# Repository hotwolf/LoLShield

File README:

This is the website of the LoLSnakes project.

...see https://hotwolf.github.io/LoLSnakes/

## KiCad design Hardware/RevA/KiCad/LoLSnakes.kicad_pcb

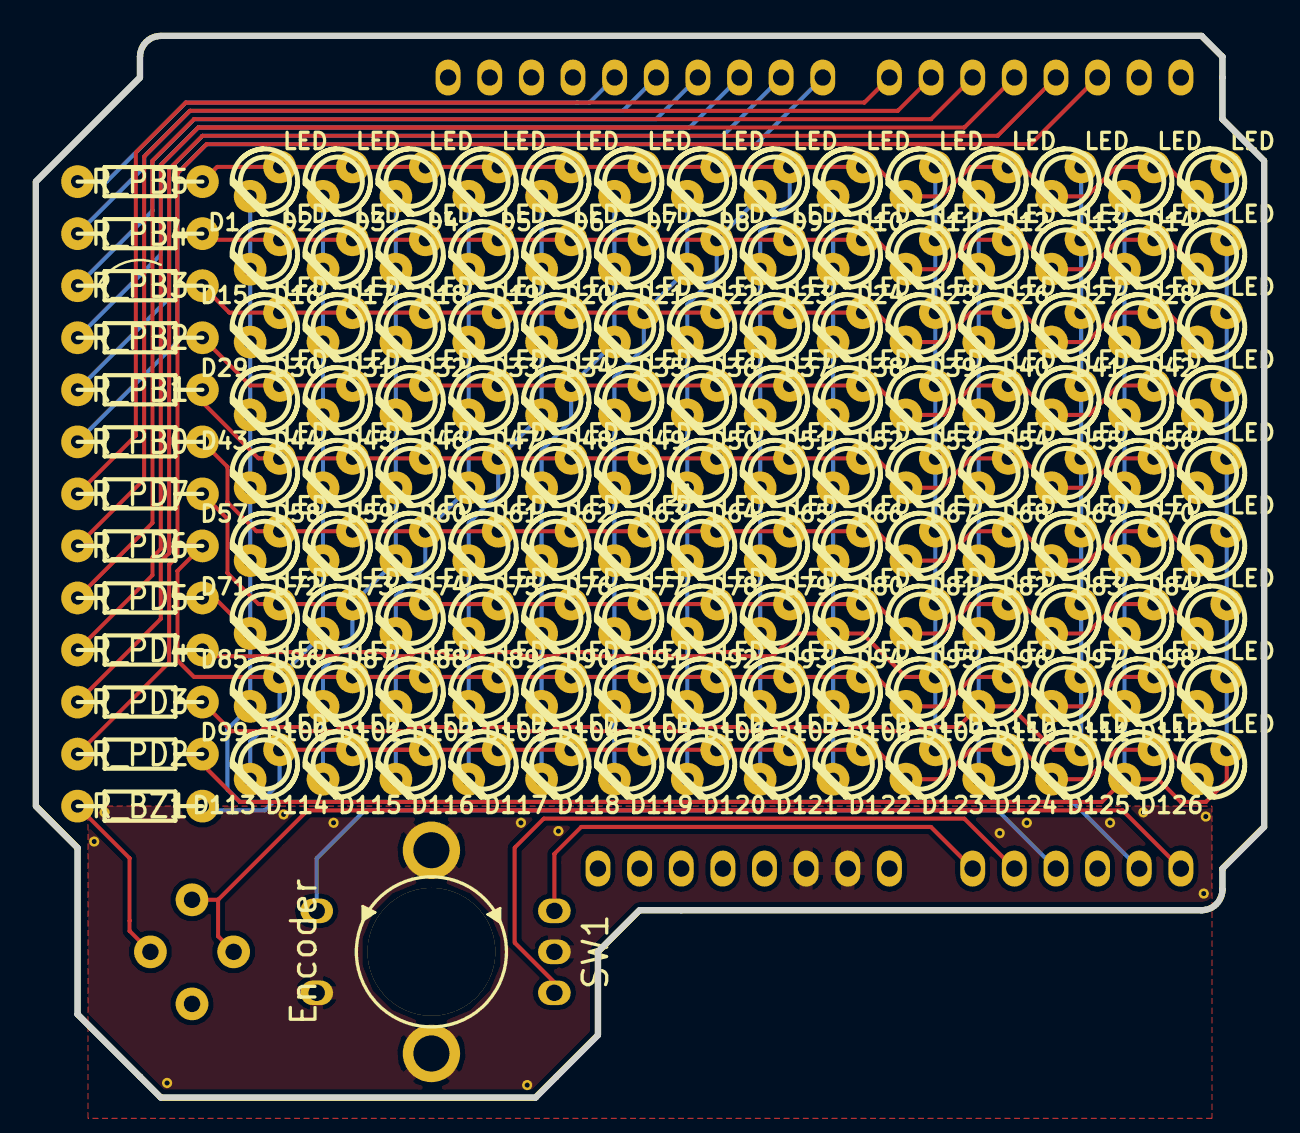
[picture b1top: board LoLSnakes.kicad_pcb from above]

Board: 2 copper layers, 74.9 x 64.8 mm, 156 parts (1 on the bottom side), 31 nets.

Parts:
BZ1: BUZZER; buzzer
D1, D2, D3, D4, D5, D6, D7, D8, D9, D10, D11, D12, D13, D14, D15, D16, D17, D18, D19, D20, D21, D22, D23, D24, D25, D26, D27, D28, D29, D30, D31, D32, D33, D34, D35, D36, D37, D38, D39, D40, D41, D42, D43, D44, D45, D46, D47, D48, D49, D50, D51, D52, D53, D54, D55, D56, D57, D58, D59, D60, D61, D62, D63, D64, D65, D66, D67, D68, D69, D70, D71, D72, D73, D74, D75, D76, D77, D78, D79, D80, D81, D82, D83, D84, D85, D86, D87, D88, D89, D90, D91, D92, D93, D94, D95, D96, D97, D98, D99, D100, D101, D102, D103, D104, D105, D106, D107, D108, D109, D110, D111, D112, D113, D114, D115, D116, D117, D118, D119, D120, D121, D122, D123, D124, D125, D126: LED; led_3mm_clear
J1: ARDUINO; arduino_header_extended
R_BZ1: R; rc03
R_PB0, R_PB1, R_PB2, R_PB3, R_PB4, R_PB5: R; rc03
R_PD2, R_PD3, R_PD4, R_PD5, R_PD6, R_PD7: R; rc03
SW1: Encoder; encoder_lowered
VIA: GND; via
VIA#2, VIA#3, VIA#4, VIA#5, VIA#6, VIA#7, VIA#8, VIA#9, VIA#10, VIA#11, VIA#12, VIA#13, VIA#14: GND; via

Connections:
/PB0: J1.23, R_PB0.1
/PB0_R: D4.1, D18.1, D32.1, D46.1, D60.1, D71.2, D72.2, D73.2, D74.2, D75.2, D76.2, D77.2, D78.2, D79.2, D80.1, D81.2, D82.1, D83.2, D84.1, D87.1, D101.1, D115.1, R_PB0.2
/PB1: J1.24, R_PB1.1
/PB1_R: D5.1, D19.1, D33.1, D47.1, D57.2, D58.2, D59.2, D60.2, D61.2, D62.2, D63.2, D64.2, D65.2, D66.1, D67.2, D68.1, D69.2, D70.1, D74.1, D88.1, D102.1, D116.1, R_PB1.2
/PB2: J1.25, R_PB2.1
/PB2_R: D6.1, D20.1, D34.1, D43.2, D44.2, D45.2, D46.2, D47.2, D48.2, D49.2, D50.2, D51.2, D52.1, D53.2, D54.1, D55.2, D56.1, D61.1, D75.1, D89.1, D103.1, D117.1, R_PB2.2
/PB3: J1.26, R_PB3.1
/PB3_R: D7.1, D21.1, D29.2, D30.2, D31.2, D32.2, D33.2, D34.2, D35.2, D36.2, D37.2, D38.1, D39.2, D40.1, D41.2, D42.1, D48.1, D62.1, D76.1, D90.1, D104.1, D118.1, R_PB3.2
/PB4: J1.27, R_PB4.1
/PB4_R: D8.1, D15.2, D16.2, D17.2, D18.2, D19.2, D20.2, D21.2, D22.2, D23.2, D24.1, D25.2, D26.1, D27.2, D28.1, D35.1, D49.1, D63.1, D77.1, D91.1, D105.1, D119.1, R_PB4.2
/PB5: J1.28, R_PB5.1
/PB5_R: D1.2, D2.2, D3.2, D4.2, D5.2, D6.2, D7.2, D8.2, D9.2, D10.1, D11.2, D12.1, D13.2, D14.1, D22.1, D36.1, D50.1, D64.1, D78.1, D92.1, D106.1, D120.1, R_PB5.2
/PD2: J1.17, R_PD2.1
/PD2_R: D13.1, D14.2, D27.1, D28.2, D41.1, D42.2, D55.1, D56.2, D69.1, D70.2, D83.1, D84.2, D97.1, D98.2, D111.1, D112.2, D125.1, D126.2, R_PD2.2
/PD3: J1.18, R_PD3.1
/PD3_R: D11.1, D12.2, D25.1, D26.2, D39.1, D40.2, D53.1, D54.2, D67.1, D68.2, D81.1, D82.2, D95.1, D96.2, D109.1, D110.2, D123.1, D124.2, R_PD3.2
/PD4: J1.19, R_PD4.1
/PD4_R: D9.1, D10.2, D23.1, D24.2, D37.1, D38.2, D51.1, D52.2, D65.1, D66.2, D79.1, D80.2, D93.1, D94.2, D107.1, D108.2, D121.1, D122.2, R_PD4.2
/PD5: J1.20, R_PD5.1
/PD5_R: D1.1, D15.1, D29.1, D43.1, D57.1, D71.1, D85.1, D99.1, D113.2, D114.2, D115.2, D116.2, D117.2, D118.2, D119.2, D120.2, D121.2, D122.1, D123.2, D124.1, D125.2, D126.1, R_PD5.2
/PD6: J1.21, R_PD6.1
/PD6_R: D2.1, D16.1, D30.1, D44.1, D58.1, D72.1, D86.1, D99.2, D100.2, D101.2, D102.2, D103.2, D104.2, D105.2, D106.2, D107.2, D108.1, D109.2, D110.1, D111.2, D112.1, D113.1, R_PD6.2
/PD7: J1.22, R_PD7.1
/PD7_R: D3.1, D17.1, D31.1, D45.1, D59.1, D73.1, D85.2, D86.2, D87.2, D88.2, D89.2, D90.2, D91.2, D92.2, D93.2, D94.1, D95.2, D96.1, D97.2, D98.1, D100.1, D114.1, R_PD7.2
GND: J1.6, J1.7, SW1.2, SW1.5, SW1.6, VIA.1, VIA#2.1, VIA#3.1, VIA#4.1, VIA#5.1, VIA#6.1, VIA#7.1, VIA#8.1, VIA#9.1, VIA#10.1, VIA#11.1, VIA#12.1, VIA#13.1, VIA#14.1
unnamed: BZ1.1, J1.14
unnamed: BZ1.2, R_BZ1.2
unnamed: J1.9, SW1.3
unnamed: J1.10, SW1.1
unnamed: J1.11, SW1.4
unnamed: J1.13, R_BZ1.1

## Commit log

2018-05-14 initial release
2018-06-07 updated buzzer footprint
2018-06-07 initial web site
2018-06-08 updated 404 page
2018-06-11 updated related projects
